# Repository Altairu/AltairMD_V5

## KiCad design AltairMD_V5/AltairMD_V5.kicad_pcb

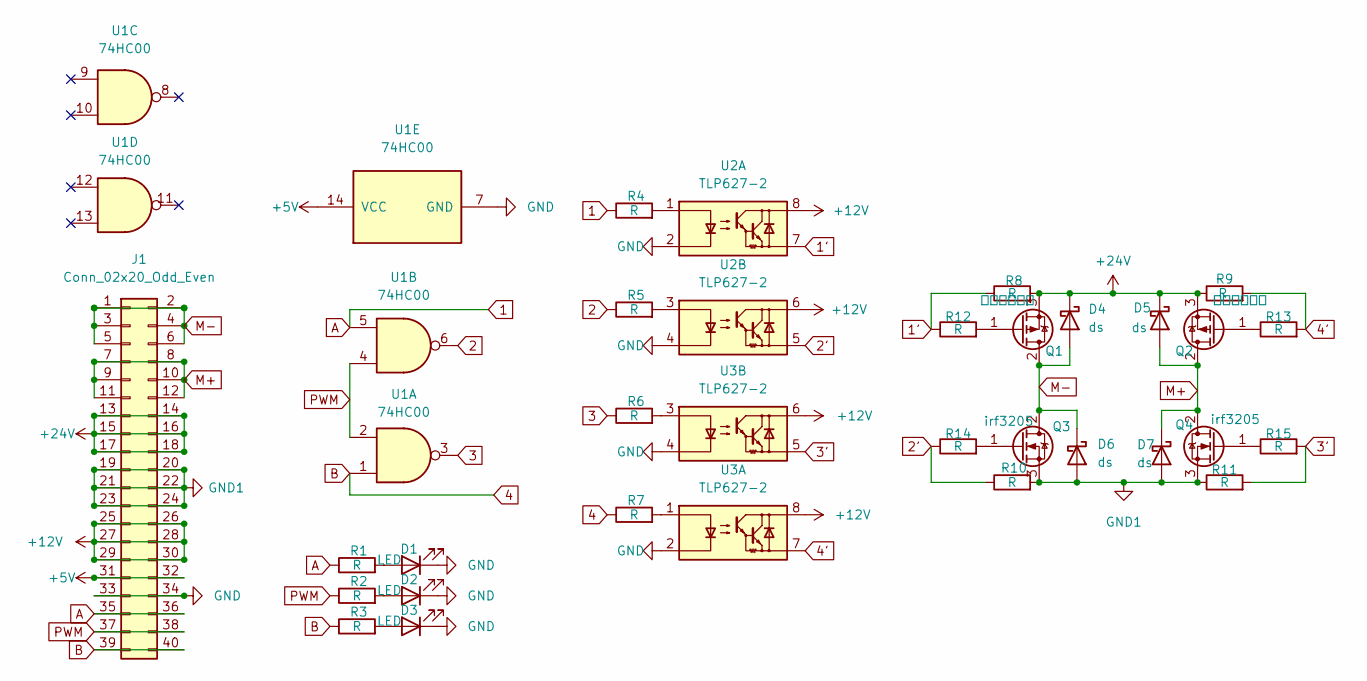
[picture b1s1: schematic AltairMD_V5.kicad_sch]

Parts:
D1, D2, D3: LED; LED_D3.0mm
D4, D5, D6, D7: ds; D_DO-41_SOD81_P10.16mm_Horizontal
J1: Conn_02x20_Odd_Even; PinHeader_2x20_P2.54mm_Horizontal
Q1, Q2: ２ＳＪ３３４; TO-220-3_Vertical
Q3, Q4: irf3205; TO-220-3_Vertical
R1, R2, R3, R4, R5, R6, R7, R8, R9, R10, R11, R12, R13, R14, R15: R; R_Axial_DIN0207_L6.3mm_D2.5mm_P10.16mm_Horizontal
U1: 74HC00; DIP-14_W7.62mm
U2, U3: TLP627-2; DIP-8_W7.62mm

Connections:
1: J1.35, J1.36, R1.1, R4.1, U1.5
1': R8.1, R12.1, U2.7
2: R5.1, U1.6
2': R10.1, R14.1, U2.5
3: R6.1, U1.3
3': R11.2, R15.2, U3.5
4: J1.39, J1.40, R3.1, R7.1, U1.1
4': R9.2, R13.2, U3.7
+5V: J1.31, J1.32, U1.14 (VCC)
+12V: J1.25, J1.26, J1.27, J1.28, J1.29, J1.30, U2.6, U2.8, U3.6, U3.8
+24V: D4.1 (K), D5.1 (K), J1.13, J1.14, J1.15, J1.16, J1.17, J1.18, Q1.3 (S), Q2.3 (S), R8.2, R9.1
GND: D1.1 (K), D2.1 (K), D3.1 (K), J1.33, J1.34, U1.7 (GND), U2.2, U2.4, U3.2, U3.4
GND1: D6.2 (A), D7.2 (A), J1.19, J1.20, J1.21, J1.22, J1.23, J1.24, Q3.3 (S), Q4.3 (S), R10.2, R11.1
M+: D5.2 (A), D7.1 (K), J1.7, J1.8, J1.9, J1.10, J1.11, J1.12, Q2.2 (D), Q4.2 (D)
M-: D4.2 (A), D6.1 (K), J1.1, J1.2, J1.3, J1.4, J1.5, J1.6, Q1.2 (D), Q3.2 (D)
unnamed: D1.2 (A), R1.2
unnamed: D2.2 (A), R2.2
unnamed: D3.2 (A), R3.2
unnamed: Q1.1 (G), R12.2
unnamed: Q2.1 (G), R13.1
unnamed: Q3.1 (G), R14.2
unnamed: Q4.1 (G), R15.1
unnamed: R4.2, U2.1
unnamed: R5.2, U2.3
unnamed: R6.2, U3.3
unnamed: R7.2, U3.1
PWM: J1.37, J1.38, R2.1, U1.2, U1.4

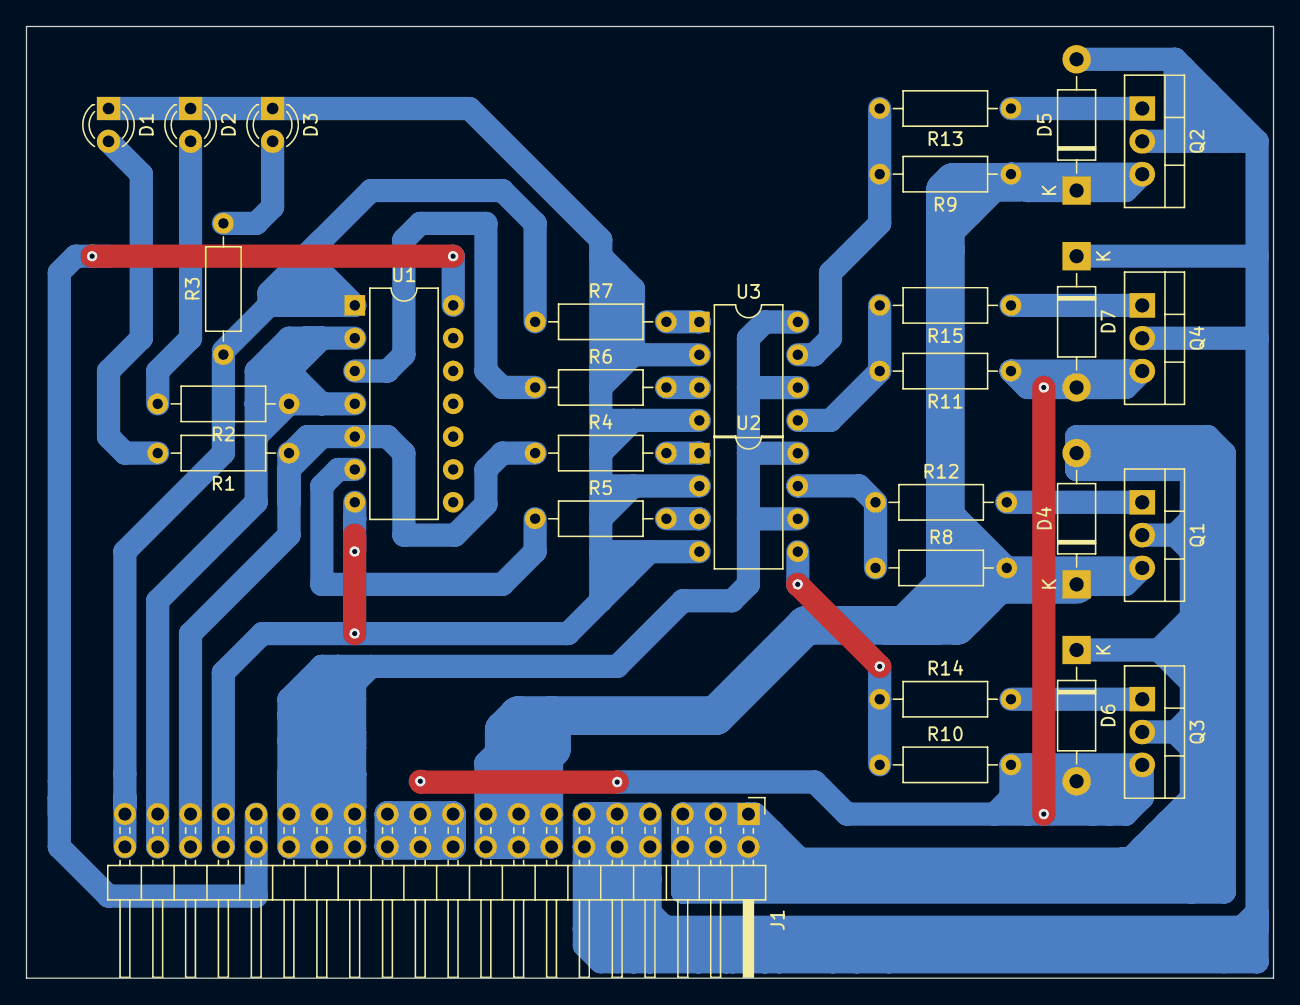
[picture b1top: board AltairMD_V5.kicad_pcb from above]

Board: 2 copper layers, 96.5 x 73.7 mm, 30 parts (0 on the bottom side), 27 nets.
